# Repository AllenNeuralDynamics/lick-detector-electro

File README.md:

# Lick Detector Electro

This is a migration of the [Dual Lick Port](https://www.janelia.org/open-science/dual-lick-port-detector)
from [Janelia Research Campus](https://www.janelia.org/).

## Device Overview

The Dual Lick Port uses a [two-transistor amplifier circuit](https://www.electronics-notes.com/articles/analogue_circuits/transistor/amplifier-npn-pnp-two-transistor-circuit.php)
to detect licks from an instrumented lick port where the mouse receives liquids.
This detection circuit can be operated isolated or non-isolated from the output
signal made available on each Lick Port.

Lick Ports can be plugged directly into a a Harp Behavior Device Port as-is
with a CAT6 cable.

This board also exposes each Lick Port's 12V output via the two Molex Microfit
3 sockets on the top-and-bottom right side of the board.

## Connection Overview

## Schematic

[schematic.pdf](./board/JF-SV-LP0001.pdf)

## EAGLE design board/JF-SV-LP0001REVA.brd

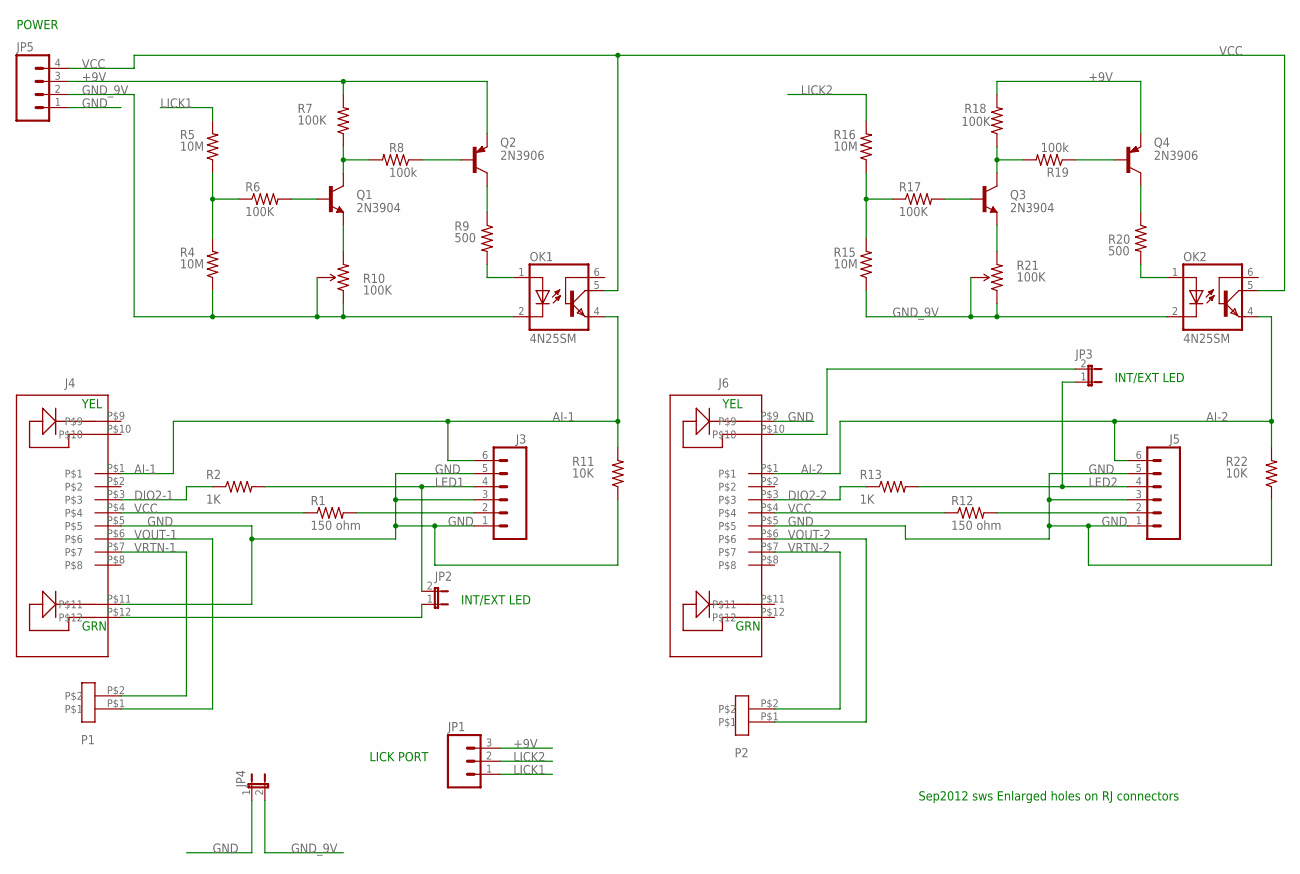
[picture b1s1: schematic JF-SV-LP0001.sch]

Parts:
J3, J5: M063.5MM-6; SCREWTERMINAL-3.5MM-6
J4, J6: RJ45_LED
JP1: M03POLAR; MOLEX-1X3
JP2, JP3: JP1E; JP1
JP4: JUMPER-2PTH; 1X02
JP5: M04POLAR; MOLEX-1X4
OK1, OK2: 4N25SM; DIL6-SMD
P1, P2: CON2MICRO-FIT; MICRO-FIT-2-RA
Q1, Q3: 2N3904; SOT23-BEC
Q2, Q4: 2N3906; SOT23-BEC
R1, R12: 150 ohm; 0805S
R2, R13: 1K; 0805S
R4, R5, R15, R16: 10M; 0805S
R6, R7, R17, R18: 100K; 0805S
R8, R19: 100k; 0805S
R9, R20: 500; 0805S
R10, R21: 100K; TRIM_POT_PTH
R11, R22: 10K; 0805S

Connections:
+9V: JP1.3, JP5.3, Q2.E, Q4.E, R7.2, R18.2
AI-1: J3.6, J4.P$1, OK1.4 (EMI), R11.2
AI-2: J5.6, J6.P$1, OK2.4 (EMI), R22.2
DIO2-1: J4.P$3, R2.1
DIO2-2: J6.P$3, R13.1
GND: J3.1, J3.3, J3.5, J4.P$5, J4.P$11, J5.1, J5.3, J5.5, J6.P$5, J6.P$9, JP4.1, JP5.1, R11.1, R22.1
GND_9V: JP4.2, JP5.2, OK1.2 (C), OK2.2 (C), R4.1, R10.1 (CCW), R10.2 (WIPER), R15.1, R21.1 (CCW), R21.2 (WIPER)
LED1: J3.4, JP2.2, R2.2
LED2: J5.4, JP3.1, R13.2
LICK1: JP1.1, R5.2
LICK2: JP1.2, R16.2
unnamed: J3.2, R1.2
unnamed: OK1.1 (A), R9.2
unnamed: J4.P$12, JP2.1
unnamed: R4.2, R5.1, R6.1
unnamed: Q1.B, R6.2
unnamed: Q1.E, R10.3 (CW)
unnamed: Q1.C, R7.1, R8.2
unnamed: Q2.B, R8.1
unnamed: Q2.C, R9.1
unnamed: J6.P$10, JP3.2
unnamed: J5.2, R12.2
unnamed: R15.2, R16.1, R17.1
unnamed: Q3.B, R17.2
unnamed: Q3.E, R21.3 (CW)
unnamed: Q3.C, R18.1, R19.2
unnamed: Q4.B, R19.1
unnamed: OK2.1 (A), R20.2
unnamed: Q4.C, R20.1
VCC: J4.P$4, J6.P$4, JP5.4, OK1.5 (COL), OK2.5 (COL), R1.1, R12.1
VOUT-1: J4.P$6, P1.P$1
VOUT-2: J6.P$6, P2.P$1
VRTN-1: J4.P$7, P1.P$2
VRTN-2: J6.P$7, P2.P$2

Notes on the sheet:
LICK PORT
POWER
YEL
GRN
INT/EXT LED
Sep2012 sws Enlarged holes on RJ connectors

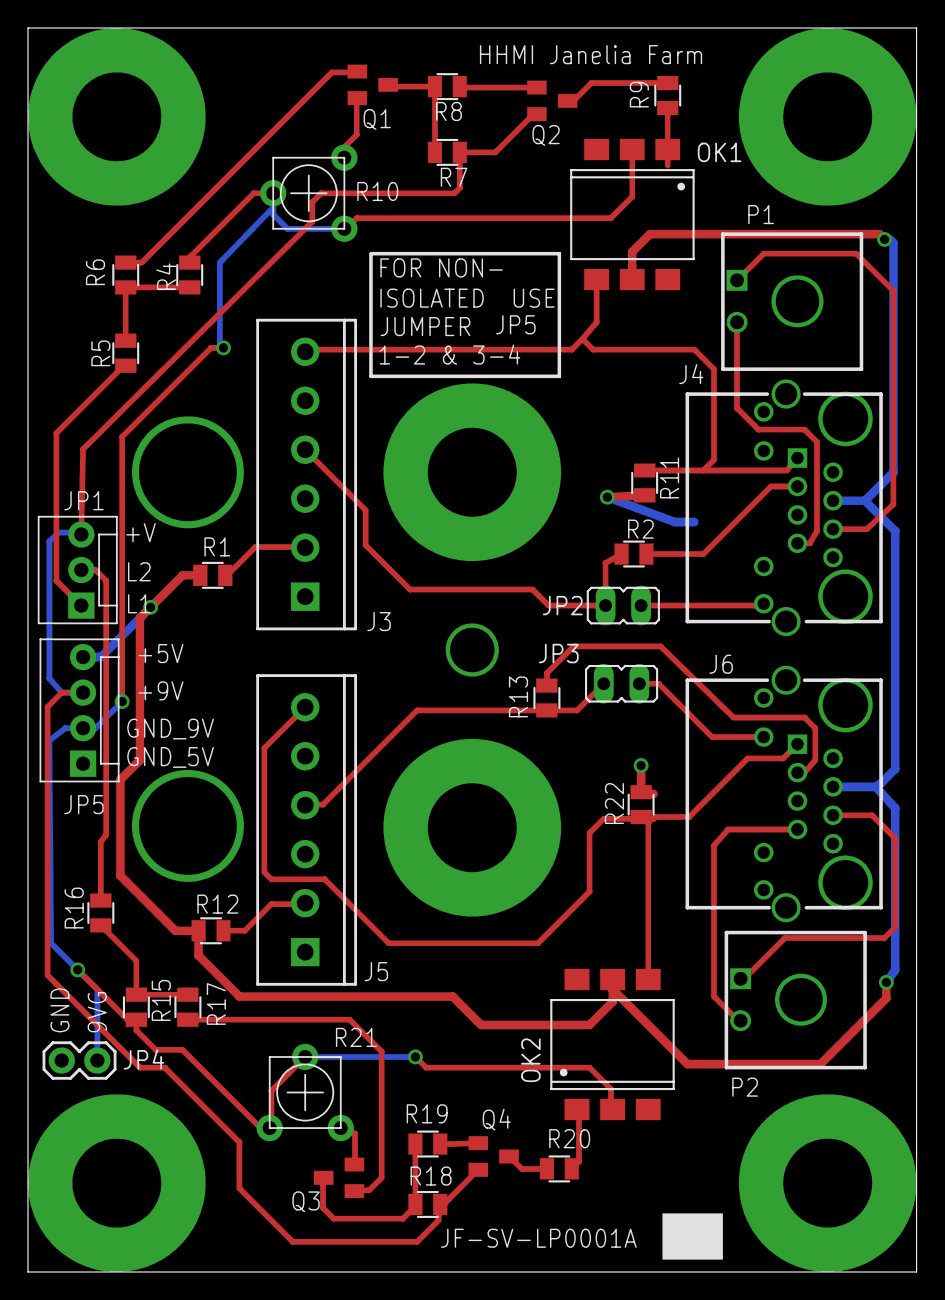
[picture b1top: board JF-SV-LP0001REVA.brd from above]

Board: 2 copper layers, 63.5 x 88.9 mm, 37 parts (0 on the bottom side), 34 nets.

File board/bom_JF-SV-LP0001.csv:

Schematic Component,Circuit Component,Part Number from Digi-Key,Quantity,Cost/,Cost Total,,
"JP2, JP3, JP4 ",2 Pin Header,609-3506-ND,3,$0.26,$0.78,,30
"P1, P2",2 Pin Connector,WM1860-ND,2,$0.84,$1.68,,20
JP1,3 Pin Header,WM4201-ND,1,$0.30,$0.30,,10
JP5,4 Pin Header,WM4202-ND,1,$0.37,$0.37,,10
"J4, J6",RJ45 with LEDs,RJHSE-3081-ND,2,$2.54,$5.08,,20
"J3, J5",TERM BLOCK 6POS SIDE ENT 3.5MM,A98162-ND,2,$2.67,$5.34,,20
"OK1, OK2",OPTOCOUPLER TRANS-OUT 6-SMD,4N25SM-ND,2,$0.57,$1.14,,20
"R1, R12","Resistor, 150 ohms, 1%, 0805",P150CCT-ND,2,$0.10,$0.20,,20
"R2, R13","Resistor, 1.0K, 1%, 0805",541-1.00KCCT-ND,2,$0.10,$0.20,,20
"R9, R20","Resistor, 499 ohms, 1%, 0805",541-499CCT-ND,2,$0.10,$0.20,,20
"R6, R7, R8, R17, R18, R19 ","Resistor, 100K, 1%, 0805",P100KCCT-ND,6,$0.10,$0.60,,60
"R4, R5, R15, R16","Resistor, 10.0M, 1%, 0805",541-10.0MCCT-ND,4,$0.10,$0.40,,40
"R11, R22","Resistor, 10.0K, 1%, 0805",541-10.0KCCT-ND,2,$0.10,$0.20,,20
"R10, R21","Trim Pot, 100K, top adjust",3386P-104LF-ND,2,$1.24,$2.48,,20
"Q1, Q3",TRANS NPN 40V 200MA SOT23,568-4510-1-ND,2,$0.14,$0.28,,20
"Q2, Q4",TRANSISTOR GP PNP AMP SOT-23,MMBT3906FSCT-ND,2,$0.17,$0.34,,20
Shunt Jumpers (as required),"2 pos, 0.1” center",A26242-ND,4,$0.31,$1.24,,40
PCB,,,1,$14.58,$14.58,,
,,,,,,,
,,,,,$35.41,,

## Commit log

2022-04-26 adding board pdf
2022-04-27 adding folder for pics
2022-04-27 adding references
2022-04-27 adding janelia license
2022-04-27 adding illustrator file and up-to-date png
2022-05-12 README: move references and errata into github wiki
2022-05-12 README: link to original Janelia project page
2022-05-12 convert BOM to CSV
2022-05-12 remove "REVA" from filenames
    We don't know what Rev A is, in relation to the boards that were actually
    produced. Once we produce our own boards, we will mark them with our own
    semantic versioning scheme and tag the applicable commit with that version
    number in this repo.
2022-08-19 fixing broken schematic link
